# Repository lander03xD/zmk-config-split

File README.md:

# ZMK-CONFIG-SPLIT 

This is a keyboard made with a pcb in a split layout with 36 keys and a promicro nrf52840 as the microcontroller.

zmk documentation: zmk.dev
todo: add picture of keyboard

# LAYOUT

There are by default 4 layers and 2 extra's if you want to add more in zmk studio:
* base 
* symbols
* navigation
* config

Documentation pdf can be found in the docs folder: [keymap_explained.pdf](https://github.com/lander03xD/zmk-config-split/blob/main/docs/keymap_explained.pdf).

# Building the keyboard

This section is just for you Glen! (do ask questions)

CAUTION:
* Diodes are directional.
* Left powerlines need to be corrected.
* Always test your progress with a multimeter. 

Order of doing things:
 
* **DIODES:**
* NOTE: I put the diodes on the bottom of the board so that I can easily fix one if they are broken at some point. Diodes are directional, so put them in the right orientation.
* Bend the diodes over the powerswitch. The powerswitch is the right width so that you can easily bend the legs and insert them in the keyboard later.
* Insert all diodes. CAUTION! Diodes are directional. You can see the flow the diode allows by checking the little black line on the diode. This line should point towards the bottom of the keyboard.
* I soldered the diodes on the bottom of the board. Flip the board and solder on the legs. 
* **HEADER PINS:**
* You need a row of 12 headerpins. Count them carefully. 
* Cut off the excess. You will need the spacer on the remaining pins to lift up the edges of the microcontroller. Pull the spacers of the remaining pins and slide em on the long end of the first and last pin you will use.
* Put the diode pins on the board, and solder 1 singular pin! Reflow the solder and make sure the headerpins are straight on the PCB. If both rows of header pins are connected with a single pin. You can test out the fit with the microcontroller. before soldering in the other pins. DON'T SOLDER THE MICROCONTROLLER YET.
* **POWER SWITCH**
* Solder in the powerswitch. Orionation doens't matter. Do solder in one leg before you reflow the solder to make sure it's straight on the board.
* **FIX POWER LINES**
* On the left hand side of the boards the powerlines are not correct. These need to be corrected manually.
* cut the line going from the 'GND' pad to one of the pins. Cut the line going from the middle pin on the powerswitch to the microcontroller pin. See picture for reference.
* prepare 2 lengths of wire. Red is positive, black is gnd. solder on the back of the board.
* black: from the 'gnd' pad to the third pin on the right side. 
* red: from the middle pin on the powerswitch to the top pin on the left. 
* **BATTERY**
* pretin the battery pads
* disconnect the powerswitch. (down is 'off', up is 'on')
* solder the black wire of the battery to the 'gnd' pad, and the red wire to the 'B+' pad.
* **FIRMWARE**
* flashing the firmware. 
* connect the microcontroller to the pc. Short the 'gnd' and 'rst' pins (third and fourth pin on the right side) (acts as a reset button) swiftly twice. (check pinout : https://holykeebs.com/cdn/shop/files/Supermini-nRF52840-Pinout.webp )
* The orange led should start blinking and a drive should open on the computer. Drop the firmware in this drive and let it do it's thing. The led should stop blinking when the firmware is uploaded.
* Upload the left firmware to the left microcontroller, and the right to the right.
* **MCU**
* put the MCU on the headerpins on top of the battery. 
* solder in the pins. (Good luck) 
* **SWITCHES** 
* put the plate on the pcb and plop in your switches. 
* solder them on the board. 
* **TESTING**
* Connect the left side to the pc. Press some keys. Call me for debugging. 
* **DISAPPOINT**
* put on your filthy printed keycaps
* make my desappointed 
* **CASE**
* Print the case
* Put in the threaded inserts: 
* Clean up the holes in the printed case. 
* Put the threaded inserts in from the outside of the board (from the top for the plate, and the bottom for the case)
* Get your soldering iron and set it to 150-160C (should be enough to make pla moldable)
* push in the threaded insert with the soldering iron and press it flat with something else so it's very straight.
* **SCREWS AND STANDOFFS**
* Near the microcontroller there are 2 holes. Push some short screws in there and tighten a spacer on top.
* Put the acrylic cover on top and tighten with the other short screws.
* The long screws go through the threaded inserts all the way through the threaded inserts in the case. Press the keyboard down properly while screwing in the big boys. 

* **DONE**

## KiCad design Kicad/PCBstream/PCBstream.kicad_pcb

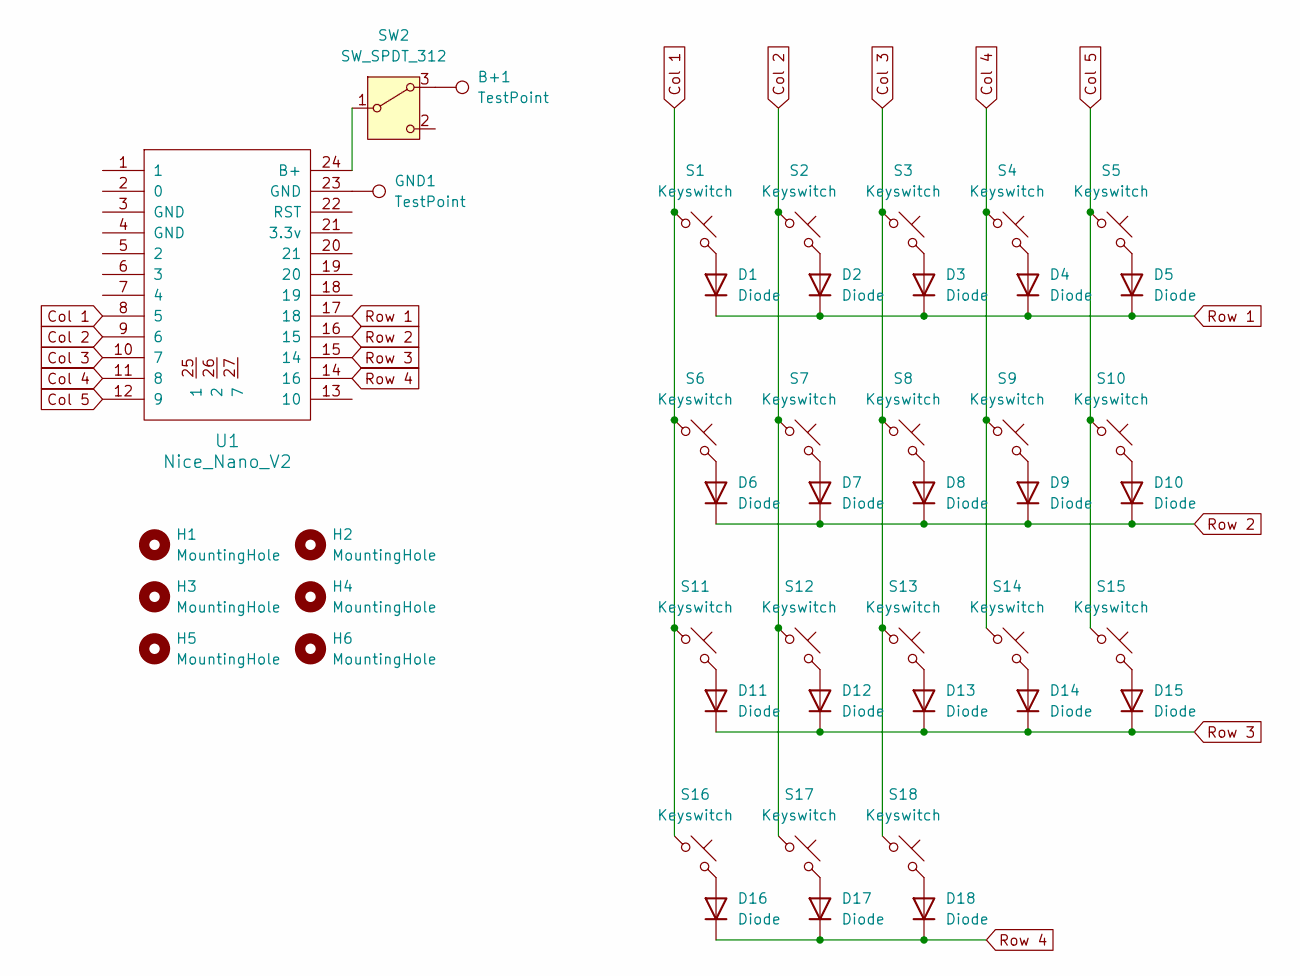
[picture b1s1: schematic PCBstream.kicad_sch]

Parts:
B+1: TestPoint; SolderWire-0.5sqmm_1x01_D0.9mm_OD2.1mm
D1, D2, D3, D4, D5, D6, D7, D8, D9, D10, D11, D12, D13, D14, D15, D16, D17, D18: Diode; Diode_DO-35
GND1: TestPoint; SolderWire-0.5sqmm_1x01_D0.9mm_OD2.1mm
H1, H2, H3, H4, H5, H6: MountingHole; MountingHole_2.2mm_M2
S1, S2, S3, S4, S5, S6, S7, S8, S9, S10, S11, S12, S13, S14, S15, S16, S17, S18: Keyswitch; MX_Solder_1.00u_Reversible
SW2: SW_SPDT_312; SW_Vertical_Slide_5mm
U1: Nice_Nano_V2

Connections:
Col 1: S1.1, S6.1, S11.1, S16.1, U1.8 (5)
Col 2: S2.1, S7.1, S12.1, S17.1, U1.9 (6)
Col 3: S3.1, S8.1, S13.1, S18.1, U1.10 (7)
Col 4: S4.1, S9.1, S14.1, U1.11 (8)
Col 5: S5.1, S10.1, S15.1, U1.12 (9)
unnamed: D1.2 (A), S1.2
unnamed: D2.2 (A), S2.2
unnamed: D3.2 (A), S3.2
unnamed: D4.2 (A), S4.2
unnamed: D5.2 (A), S5.2
unnamed: D6.2 (A), S6.2
unnamed: D7.2 (A), S7.2
unnamed: D8.2 (A), S8.2
unnamed: D9.2 (A), S9.2
unnamed: D10.2 (A), S10.2
unnamed: D11.2 (A), S11.2
unnamed: D12.2 (A), S12.2
unnamed: D13.2 (A), S13.2
unnamed: D14.2 (A), S14.2
unnamed: D15.2 (A), S15.2
unnamed: D16.2 (A), S16.2
unnamed: D17.2 (A), S17.2
unnamed: D18.2 (A), S18.2
unnamed 23: GND1.1, U1.23 (GND); also elsewhere on the board
unnamed 24: B+1.1, SW2.3 (A); also elsewhere on the board
unnamed: SW2.1 (B), U1.24 (B+)
Row 1: D1.1 (K), D2.1 (K), D3.1 (K), D4.1 (K), D5.1 (K), U1.17 (18)
Row 2: D6.1 (K), D7.1 (K), D8.1 (K), D9.1 (K), D10.1 (K), U1.16 (15)
Row 3: D11.1 (K), D12.1 (K), D13.1 (K), D14.1 (K), D15.1 (K), U1.15 (14)
Row 4: D16.1 (K), D17.1 (K), D18.1 (K), U1.14 (16)

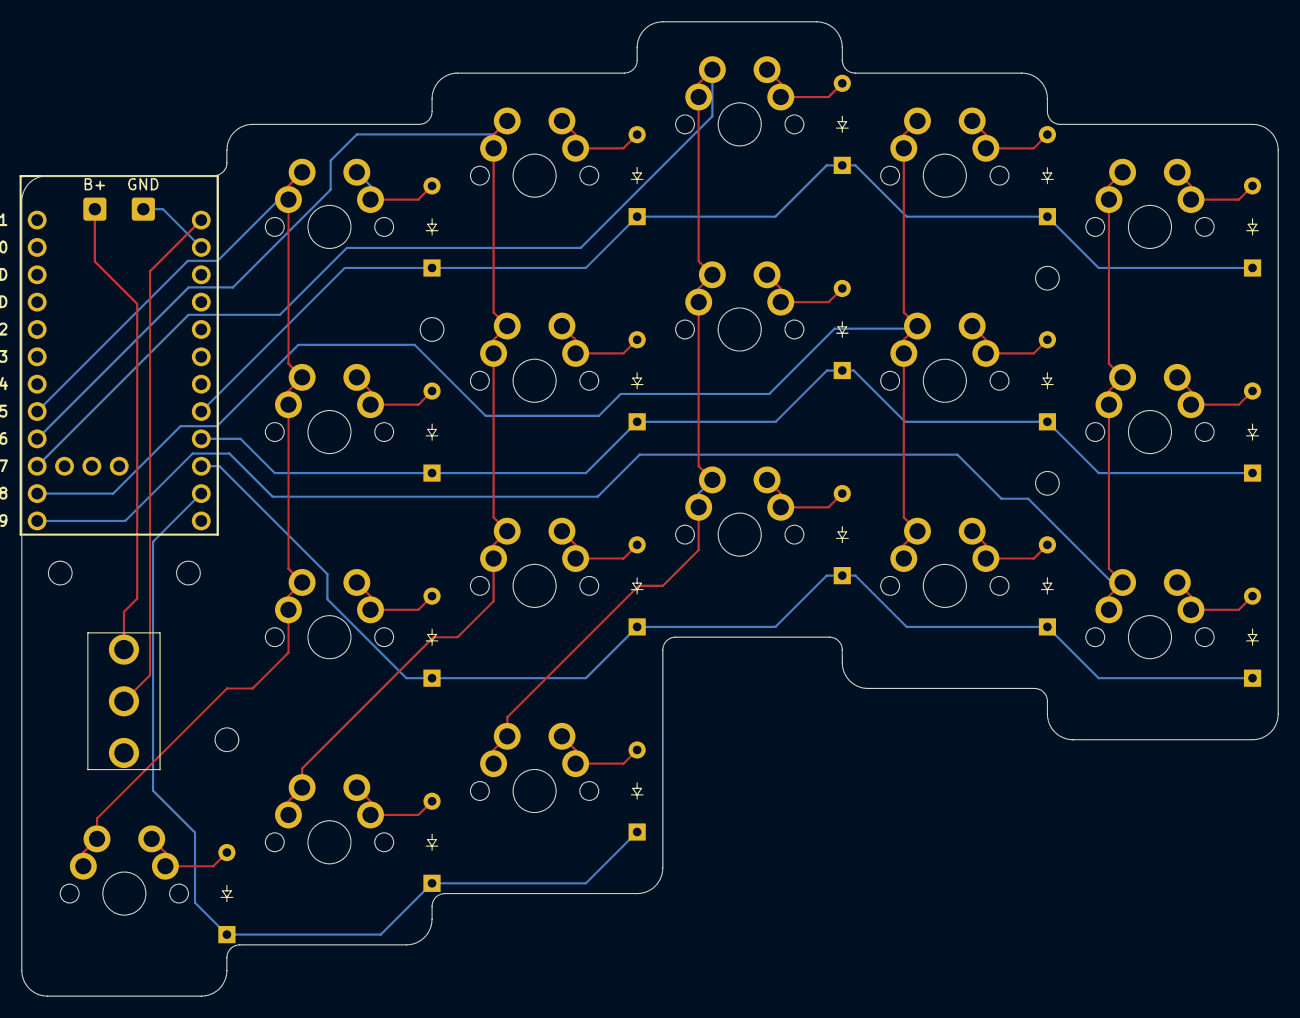
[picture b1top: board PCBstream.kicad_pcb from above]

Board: 2 copper layers, 116.7 x 90.5 mm, 46 parts (0 on the bottom side), 30 nets.

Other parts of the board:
B+: TestPoint; SolderWire-0.5sqmm_1x01_D0.9mm_OD2.1mm
GND: TestPoint; SolderWire-0.5sqmm_1x01_D0.9mm_OD2.1mm

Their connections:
unnamed 23: GND.1; also elsewhere on the board
unnamed 24: B+.1; also elsewhere on the board

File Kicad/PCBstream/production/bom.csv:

Designator,Footprint,Quantity,Value,LCSC Part #
"B+, GND",SolderWire-0.5sqmm_1x01_D0.9mm_OD2.1mm,2,TestPoint,
"D1, D10, D11, D12, D13, D14, D15, D16, D17, D18, D2, D3, D4, D5, D6, D7, D8, D9",Diode_DO-35,18,Diode,
"S1, S10, S11, S12, S13, S14, S15, S16, S17, S18, S2, S3, S4, S5, S6, S7, S8, S9",MX_Solder_1.00u_Reversible,18,Keyswitch,
SW2,SW_Vertical_Slide_5mm,1,SW_SPDT_312,
U1,Nice_Nano_V2,1,Nice_Nano_V2,

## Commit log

2025-05-18 corrected
2025-05-18 correct import
2025-05-18 removed nonexisting layers
2025-05-18 compress keybinds
2025-05-18 add another simplicity
2025-05-18 set keyboard name correctly
2025-05-18 reverse columns
2025-05-18 correction
2025-05-18 changed board
2025-05-18 undo
2025-05-18 config fix
2025-05-18 settings reset
2025-05-20 correct keymap and overlay right
2025-05-20 correct right pinouts
2025-05-27 lowered col offset
2025-05-29 added bootloader button
2025-05-29 col offset
2025-05-29 initial keymap attempt
2025-05-29 bootloader fix, homerowmod, config move
2025-05-29 hold-trigger-key-positions fix
2025-05-29 homerow mods second attempt lets go
2025-05-29 correct key
2025-05-29 keymap corrections
2025-05-29 tapping term changes
2025-05-29 layout changes
2025-05-30 remove reset button
2025-05-30 zmk studio functionality
2025-05-30 physical layout added
2025-05-30 forgotten include
2025-06-08 changed name
2025-06-09 reku
2025-06-09 rename
2025-06-12 config changes and combo
2025-06-12 change bt keys
2025-06-12 tripple build?
2025-06-12 added spaces in keyboard name
2025-06-12 extra output for build artifact
2025-06-12 changed cmake args
2025-06-12 only change name from config
2025-06-12 only change name from config 2
2025-06-12 another try
2025-06-12 santhoeusntoa
2025-06-12 just clean it up and make a build for each keyboard
2025-06-12 removed chatgpts suggestions
2025-06-13 changed holdtap behaviour and combo time
2025-06-13 documentation start
2025-06-13 reformatting table
2025-06-13 test
2025-06-13 add docs
2025-06-13 beld
2025-06-13 changed homerowmods
2025-06-15 baoesunthaosentuha
2025-06-16 rename board
2025-06-17 quick fix
2025-06-17 lowered the tapping term
2025-06-20 added keymap docs
2025-06-20 readme update
2025-06-21 added pictures s to readme
2025-06-21 added docs for glen
2025-06-22 skadi's keyboard build
2025-06-22 reku's build
2025-06-22 glen's build
2025-06-22 my own build
2025-06-22 added firmwares
2025-06-27 added kicad and freecad folders
2025-06-29 glens quick fix
2025-06-29 glens qwerty
2025-06-29 upload new glen firmware
2025-06-29 right overlay on left board
2025-06-30 updated kicad files
2025-07-03 experimental stuff for glen
2025-07-07 lets hope this fucking works cause I really am running out of ideas pleas fix
2025-07-07 one more time, are we going to celebrate??
2025-07-12 removed bond clearing on boot
2025-07-12 new firmware with remove bond on boot
2025-07-16 undo glen changes and add initial powersavings
2025-07-16 lowered polling rate for zmk matrix
2025-07-16 fix polling period syntax
2025-07-16 ble zephyr optimizations
